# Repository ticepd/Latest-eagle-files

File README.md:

# Latest-eagle-files
This repository contains latest eagle libraries/parts used in CEDT

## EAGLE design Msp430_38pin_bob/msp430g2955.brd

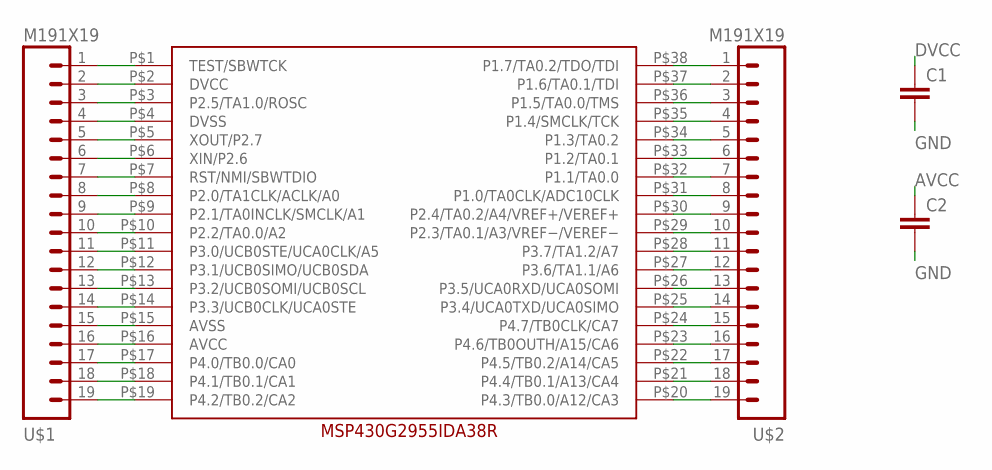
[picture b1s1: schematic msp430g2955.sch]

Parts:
C1, C2: C-EUC0805; C0805
U$1, U$2: M191X19; 1X19
U$3: MSP430G2955IDA38R

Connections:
AVCC: C2.1, U$1.16, U$3.P$16 (AVCC)
DVCC: C1.1, U$1.2, U$3.P$2 (DVCC)
GND: C1.2, C2.2, U$1.4, U$1.15, U$3.P$4 (DVSS), U$3.P$15 (AVSS)
unnamed: U$1.1, U$3.P$1 (TEST/SBWTCK)
unnamed: U$1.3, U$3.P$3 (P2.5/TA1.0/ROSC)
unnamed: U$1.5, U$3.P$5 (XOUT/P2.7)
unnamed: U$1.6, U$3.P$6 (XIN/P2.6)
unnamed: U$1.7, U$3.P$7 (RST/NMI/SBWTDIO)
unnamed: U$1.8, U$3.P$8 (P2.0/TA1CLK/ACLK/A0)
unnamed: U$1.9, U$3.P$9 (P2.1/TA0INCLK/SMCLK/A1)
unnamed: U$1.10, U$3.P$10 (P2.2/TA0.0/A2)
unnamed: U$1.11, U$3.P$11 (P3.0/UCB0STE/UCA0CLK/A5)
unnamed: U$1.12, U$3.P$12 (P3.1/UCB0SIMO/UCB0SDA)
unnamed: U$1.13, U$3.P$13 (P3.2/UCB0SOMI/UCB0SCL)
unnamed: U$1.14, U$3.P$14 (P3.3/UCB0CLK/UCA0STE)
unnamed: U$1.17, U$3.P$17 (P4.0/TB0.0/CA0)
unnamed: U$1.18, U$3.P$18 (P4.1/TB0.1/CA1)
unnamed: U$1.19, U$3.P$19 (P4.2/TB0.2/CA2)
unnamed: U$2.19, U$3.P$20 (P4.3/TB0.0/A12/CA3)
unnamed: U$2.18, U$3.P$21 (P4.4/TB0.1/A13/CA4)
unnamed: U$2.17, U$3.P$22 (P4.5/TB0.2/A14/CA5)
unnamed: U$2.16, U$3.P$23 (P4.6/TB0OUTH/A15/CA6)
unnamed: U$2.15, U$3.P$24 (P4.7/TB0CLK/CA7)
unnamed: U$2.14, U$3.P$25 (P3.4/UCA0TXD/UCA0SIMO)
unnamed: U$2.13, U$3.P$26 (P3.5/UCA0RXD/UCA0SOMI)
unnamed: U$2.12, U$3.P$27 (P3.6/TA1.1/A6)
unnamed: U$2.11, U$3.P$28 (P3.7/TA1.2/A7)
unnamed: U$2.10, U$3.P$29 (P2.3/TA0.1/A3/VREF−/VEREF−)
unnamed: U$2.9, U$3.P$30 (P2.4/TA0.2/A4/VREF+/VEREF+)
unnamed: U$2.8, U$3.P$31 (P1.0/TA0CLK/ADC10CLK)
unnamed: U$2.7, U$3.P$32 (P1.1/TA0.0)
unnamed: U$2.6, U$3.P$33 (P1.2/TA0.1)
unnamed: U$2.5, U$3.P$34 (P1.3/TA0.2)
unnamed: U$2.4, U$3.P$35 (P1.4/SMCLK/TCK)
unnamed: U$2.3, U$3.P$36 (P1.5/TA0.0/TMS)
unnamed: U$2.2, U$3.P$37 (P1.6/TA0.1/TDI)
unnamed: U$2.1, U$3.P$38 (P1.7/TA0.2/TDO/TDI)

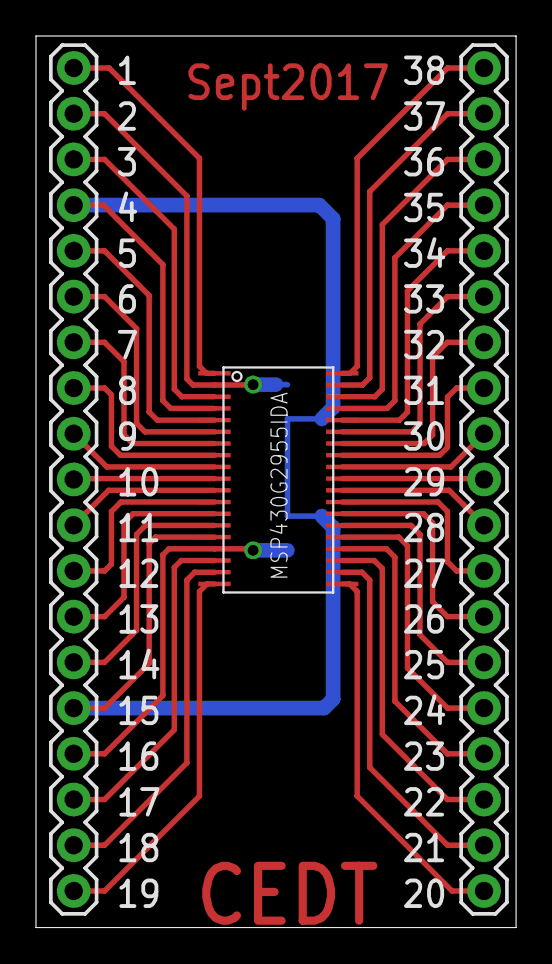
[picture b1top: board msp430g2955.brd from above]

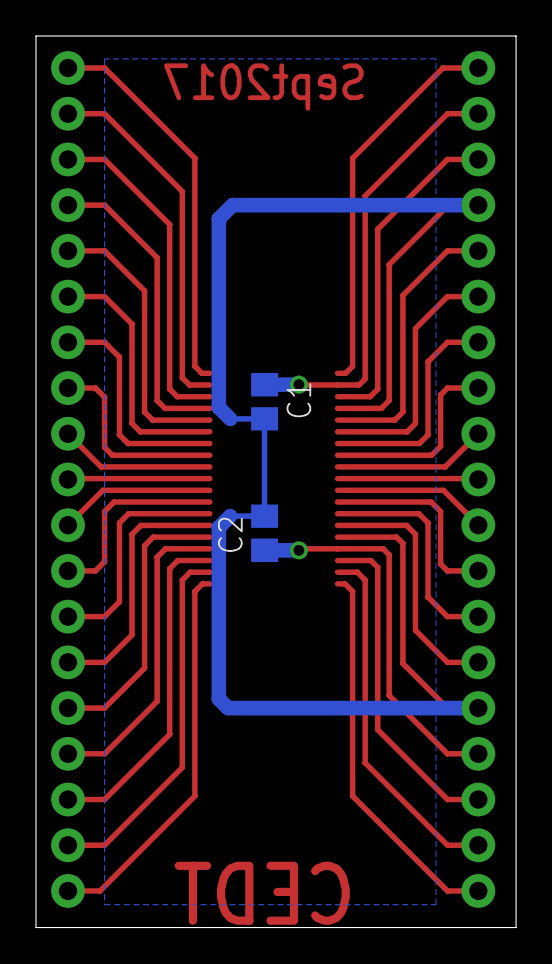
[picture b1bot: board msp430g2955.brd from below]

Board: 2 copper layers, 26.7 x 49.5 mm, 5 parts (2 on the bottom side), 37 nets.

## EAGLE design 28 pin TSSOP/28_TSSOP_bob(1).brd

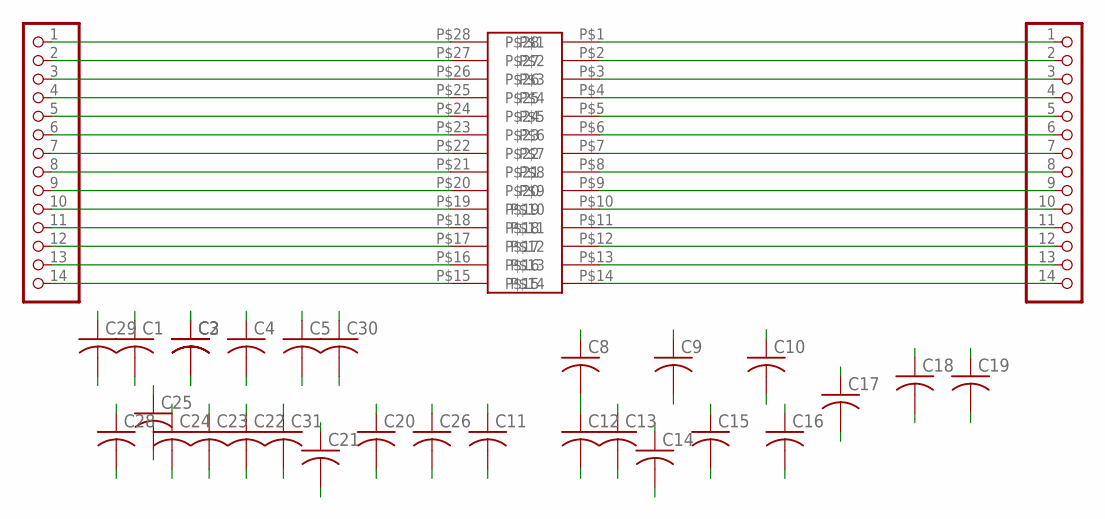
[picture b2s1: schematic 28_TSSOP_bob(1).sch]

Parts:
C1, C2, C3, C4, C5, C8, C9, C10, C11, C12, C13, C14, C15, C16, C17, C18, C19, C20, C21, C22, C23, C24, C25, C26, C28, C29, C30, C31: C-USC0805; C0805
JP1, JP2: PADS-14
U$2: 28-PINTSSOP-NW; TSSOP28-NW

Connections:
1220: C29.2
unnamed: C1.1, JP2.1, U$2.P$1
unnamed: C2.1, JP1.1, U$2.P$28
unnamed: C3.1, JP1.2, U$2.P$27
unnamed: C4.1, JP1.5, U$2.P$24
unnamed: C5.2, JP2.6, U$2.P$6
unnamed: C8.1, JP1.8, U$2.P$21
unnamed: C9.2, JP2.8, U$2.P$8
unnamed: C10.2, JP2.4, U$2.P$4
unnamed: C11.1, JP1.9, U$2.P$20
unnamed: C12.1, JP1.4, U$2.P$25
unnamed: C13.2, JP2.2, U$2.P$2
unnamed: C14.1, JP1.3, U$2.P$26
unnamed: C15.2, JP2.5, U$2.P$5
unnamed: C16.1, JP1.7, U$2.P$22
unnamed: C17.2, JP2.3, U$2.P$3
unnamed: C18.2, JP2.9, U$2.P$9
unnamed: C19.1, JP1.6, U$2.P$23
unnamed: C20.2, JP2.7, U$2.P$7
unnamed: C21.1, JP1.14, U$2.P$15
unnamed: C22.1, JP1.13, U$2.P$16
unnamed: C23.2, JP2.14, U$2.P$14
unnamed: C24.1, JP1.10, U$2.P$19
unnamed: C25.2, JP2.11, U$2.P$11
unnamed: C26.1, JP1.12, U$2.P$17
unnamed: C28.1, JP1.11, U$2.P$18
unnamed: C30.2, JP2.13, U$2.P$13
unnamed: C31.1, JP2.10, U$2.P$10
unnamed: C29.1, JP2.12, U$2.P$12

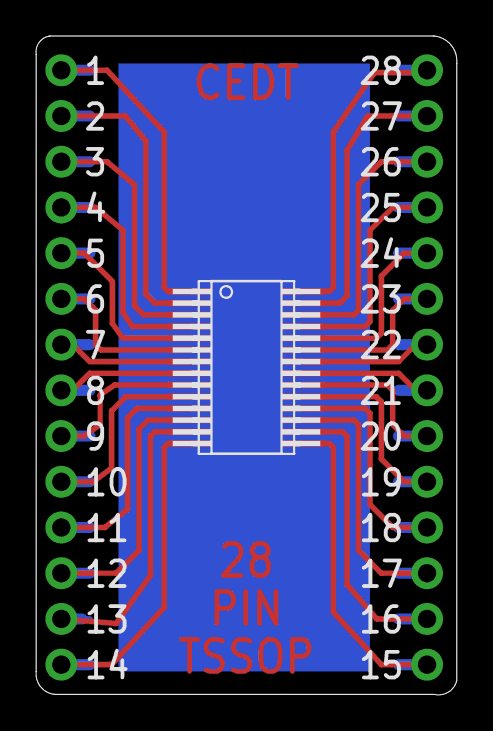
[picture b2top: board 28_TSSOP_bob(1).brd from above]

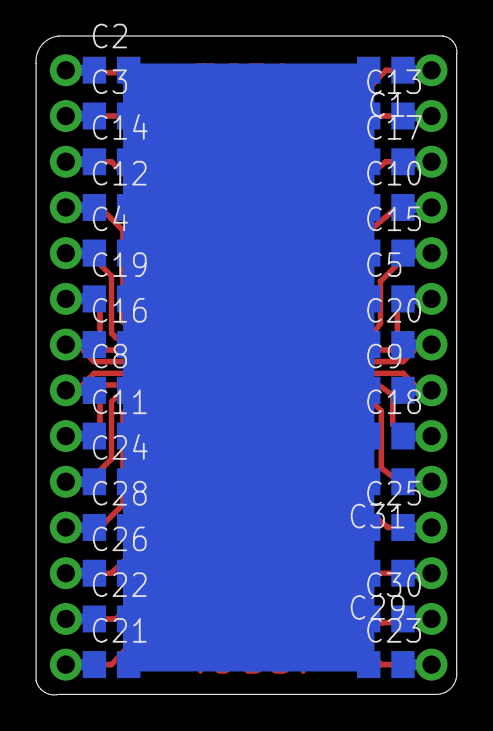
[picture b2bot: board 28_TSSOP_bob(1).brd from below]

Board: 2 copper layers, 23.4 x 36.6 mm, 31 parts (28 on the bottom side), 28 nets.

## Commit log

2017-09-05 Added files for 28 pin TSSOP package
2017-09-05 uploaded images

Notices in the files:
parts and their libraries:
SparkFun-Connectors: Licensing: Creative Commons ShareAlike 4.0 International - https://creativecommons.org/licenses/by-sa/4.0
